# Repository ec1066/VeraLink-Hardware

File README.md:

# VeraLink-Hardware
Circuit Design for VeraLink

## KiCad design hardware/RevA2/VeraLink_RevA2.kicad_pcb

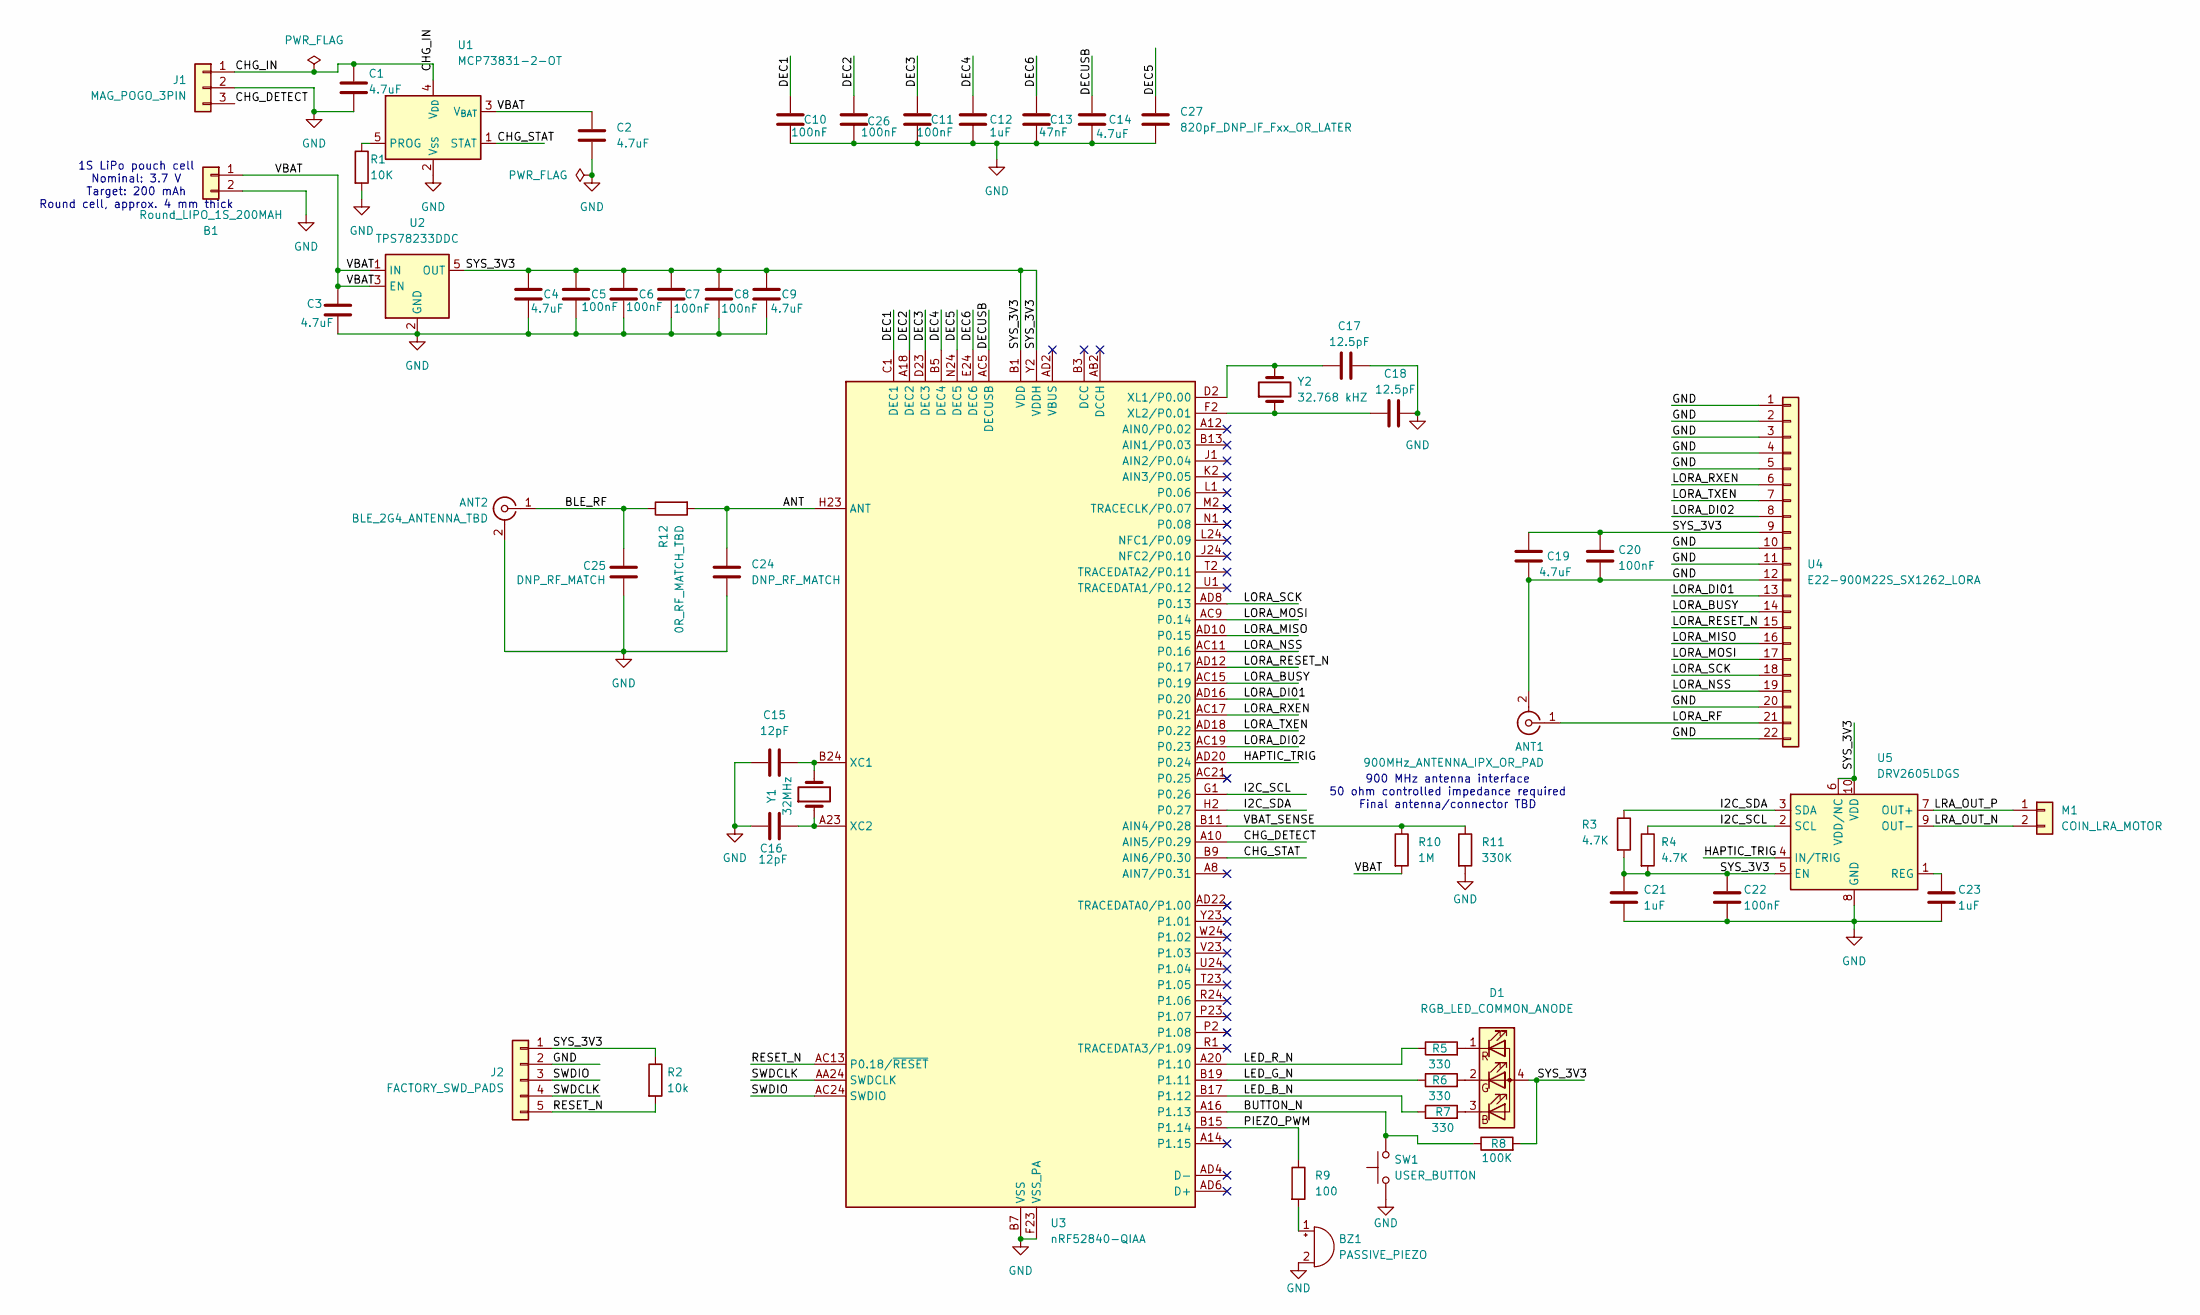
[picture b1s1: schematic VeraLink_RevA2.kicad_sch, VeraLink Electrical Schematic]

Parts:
ANT1: 900MHz_ANTENNA_IPX_OR_PAD; U.FL_Hirose_U.FL-R-SMT-1_Vertical
ANT2: BLE_2G4_ANTENNA_TBD; U.FL_Hirose_U.FL-R-SMT-1_Vertical
B1: Round_LIPO_1S_200MAH; SolderWire-0.25sqmm_1x02_P4.2mm_D0.65mm_OD1.7mm
BZ1: PASSIVE_PIEZO; SolderWire-0.25sqmm_1x02_P4.2mm_D0.65mm_OD1.7mm
C1, C2, C3, C4, C9, C14, C19: 4.7uF; C_0402_1005Metric
C5, C6, C7, C8, C10, C11, C20, C22, C26: 100nF; C_0402_1005Metric
C12, C21, C23: 1uF; C_0402_1005Metric
C13: 47nF; C_0402_1005Metric
C15, C16: 12pF; C_0402_1005Metric
C17, C18: 12.5pF; C_0402_1005Metric
C24, C25: DNP_RF_MATCH; C_0402_1005Metric
C27: 820pF_DNP_IF_Fxx_OR_LATER; C_0402_1005Metric
D1: RGB_LED_COMMON_ANODE; LED_RGB_1210
J1: MAG_POGO_3PIN; PinHeader_1x03_P2.54mm_Vertical
J2: FACTORY_SWD_PADS; VeraLink_SWD_5Pad_1x05_P1.27mm_SMD
M1: COIN_LRA_MOTOR; SolderWire-0.25sqmm_1x02_P4.2mm_D0.65mm_OD1.7mm
R1: 10K; R_0402_1005Metric
R2: 10k; R_0402_1005Metric
R3, R4: 4.7K; R_0402_1005Metric
R5, R6, R7: 330; R_0402_1005Metric
R8: 100K; R_0402_1005Metric
R9: 100; R_0402_1005Metric
R10: 1M; R_0402_1005Metric
R11: 330K; R_0402_1005Metric
R12: 0R_RF_MATCH_TBD; R_0402_1005Metric
SW1: USER_BUTTON; SW_SPST_EVQP7A
U1: MCP73831-2-OT; SOT-23-5
U2: TPS78233DDC; SOT-23-5
U3: nRF52840-QIAA; Nordic_AQFN-73-1EP_7x7mm_P0.5mm
U4: E22-900M22S_SX1262_LORA; Ebyte_E22-900M22S_22Pin_20x14mm
U5: DRV2605LDGS; TSSOP-10_3x3mm_P0.5mm
Y1: 32MHz; Crystal_SMD_2016-4Pin_2.0x1.6mm
Y2: 32.768 kHZ; Crystal_SMD_3215-2Pin_3.2x1.5mm

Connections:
/ANT: C24.1, R12.2, U3.H23 (ANT)
/BLE_RF: ANT2.1 (In), C25.1, R12.1
/BUTTON_N: R8.1, SW1.2, U3.A16 (P1.13)
/CHG_DETECT: J1.3, U3.A10 (AIN5/P0.29)
/CHG_IN: C1.1, J1.1, U1.4 (V_{DD})
/CHG_STAT: U1.1 (STAT), U3.B9 (AIN6/P0.30)
/DEC1: C10.1, U3.C1 (DEC1)
/DEC2: C26.1, U3.A18 (DEC2)
/DEC3: C11.1, U3.D23 (DEC3)
/DEC4: C12.1, U3.B5 (DEC4)
/DEC5: C27.1, U3.N24 (DEC5)
/DEC6: C13.1, U3.E24 (DEC6)
/DECUSB: C14.1, U3.AC5 (DECUSB)
/HAPTIC_TRIG: U3.AD20 (P0.24), U5.4 (IN/TRIG)
/I2C_SCL: R4.1, U3.G1 (P0.26), U5.2 (SCL)
/I2C_SDA: R3.1, U3.H2 (P0.27), U5.3 (SDA)
/LED_B_N: R7.1, U3.B17 (P1.12)
/LED_G_N: R6.1, U3.B19 (P1.11)
/LED_R_N: R5.1, U3.A20 (P1.10)
/LORA_BUSY: U3.AC15 (P0.19), U4.14
/LORA_DI01: U3.AD16 (P0.20), U4.13
/LORA_DI02: U3.AC19 (P0.23), U4.8
/LORA_MISO: U3.AD10 (P0.15), U4.16
/LORA_MOSI: U3.AC9 (P0.14), U4.17
/LORA_NSS: U3.AC11 (P0.16), U4.19
/LORA_RESET_N: U3.AD12 (P0.17), U4.15
/LORA_RF: ANT1.1 (In), U4.21
/LORA_RXEN: U3.AC17 (P0.21), U4.6
/LORA_SCK: U3.AD8 (P0.13), U4.18
/LORA_TXEN: U3.AD18 (P0.22), U4.7
/LRA_OUT_N: M1.2, U5.9 (OUT-)
/LRA_OUT_P: M1.1, U5.7 (OUT+)
/PIEZO_PWM: R9.1, U3.B15 (P1.14)
/RESET_N: J2.5, R2.2, U3.AC13 (P0.18/~RESET)
/SWDCLK: J2.4, U3.AA24 (SWDCLK)
/SWDIO: J2.3, U3.AC24 (SWDIO)
/SYS_3V3: C4.1, C5.1, C6.1, C7.1, C8.1, C9.1, C19.2, C20.1, C21.1, C22.1, D1.4 (A), J2.1, R2.1, R3.2, R4.2, R8.2, U2.5 (OUT), U3.A22 (VDD), U3.AD14 (VDD), U3.AD23 (VDD), U3.B1 (VDD), U3.W1 (VDD), U3.Y2 (VDDH), U4.9, U5.5 (EN), U5.6 (VDD/NC), U5.10 (VDD)
/VBAT: B1.1, C2.1, C3.1, R10.2, U1.3 (V_{BAT}), U2.1 (IN), U2.3 (EN)
/VBAT_SENSE: R10.1, R11.1, U3.B11 (AIN4/P0.28)
GND: ANT1.2 (Ext), ANT2.2 (Ext), B1.2, BZ1.2 (-), C1.2, C2.2, C3.2, C4.2, C5.2, C6.2, C7.2, C8.2, C9.2, C10.2, C11.2, C12.2, C13.2, C14.2, C15.1, C16.1, C17.2, C18.2, C19.1, C20.2, C21.2, C22.2, C23.2, C24.2, C25.2, C26.2, C27.2, J1.2, J2.2, R1.2, R11.2, SW1.1, U1.2 (V_{SS}), U2.2 (GND), U2.4 (GND), U3.B7 (VSS), U3.EP (VSS), U3.F23 (VSS_PA), U4.1, U4.2, U4.3, U4.4, U4.5, U4.10, U4.11, U4.12, U4.20, U4.22, U5.8 (GND)
unnamed: BZ1.1 (+), R9.2
unnamed: D1.3 (BK), R7.2
unnamed: D1.2 (GK), R6.2
unnamed: D1.1 (RK), R5.2
unnamed: R1.1, U1.5 (PROG)
unnamed: C15.2, U3.B24 (XC1), Y1.2
unnamed: C16.2, U3.A23 (XC2), Y1.1
unnamed: C17.1, U3.D2 (XL1/P0.00), Y2.2
unnamed: C18.1, U3.F2 (XL2/P0.01), Y2.1
unnamed: C23.1, U5.1 (REG)

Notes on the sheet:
900 MHz antenna interface 50 ohm controlled impedance required Final antenna/connector TBD
1S LiPo pouch cell Nominal: 3.7 V Target: 200 mAh Round cell, approx. 4 mm thick

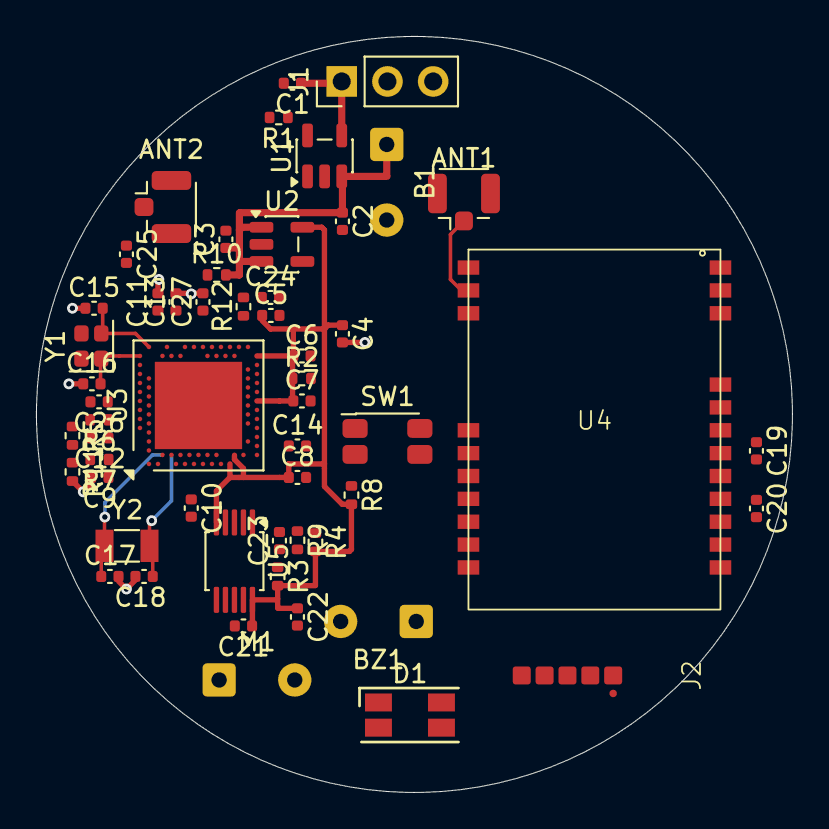
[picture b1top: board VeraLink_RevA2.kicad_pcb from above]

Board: 4 copper layers, 42.0 x 42.0 mm, 55 parts (0 on the bottom side), 50 nets.
